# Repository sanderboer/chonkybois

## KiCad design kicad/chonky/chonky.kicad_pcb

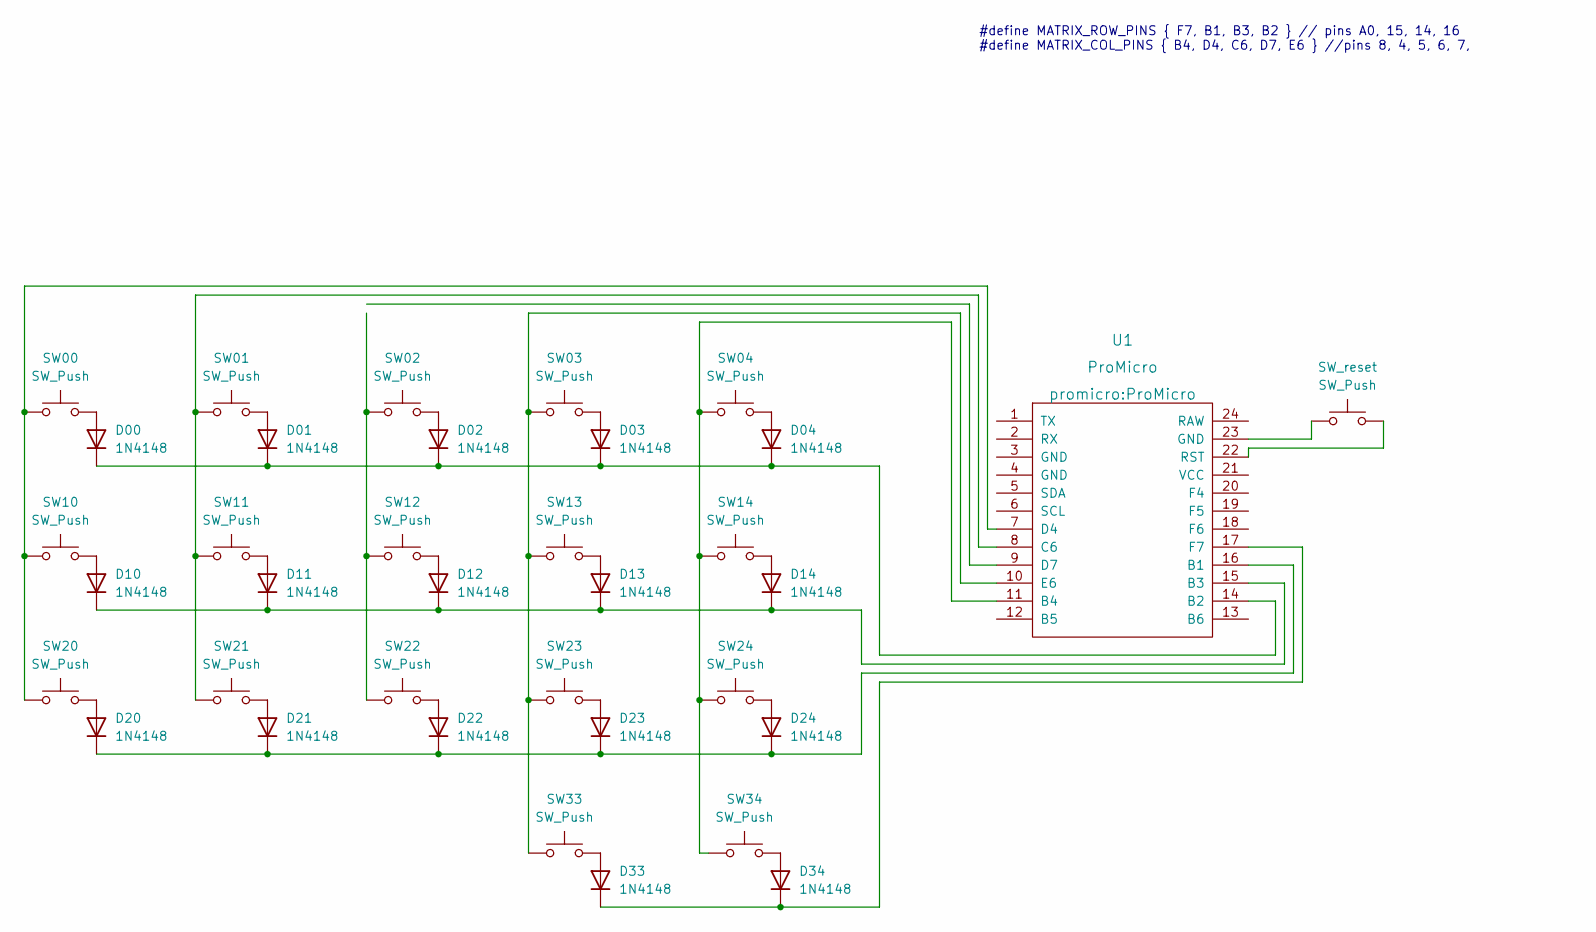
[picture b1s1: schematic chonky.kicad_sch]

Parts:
D00, D01, D02, D03, D04, D10, D11, D12, D13, D14, D20, D21, D22, D23, D24, D33, D34: 1N4148; D_DO-35_SOD27_P7.62mm_Horizontal
SW00, SW01, SW02, SW03, SW04, SW10, SW11, SW12, SW13, SW14, SW20, SW21, SW22, SW23, SW24, SW33, SW34: SW_Push; Kailh_socket_MX
SW_reset: SW_Push; Kailh_socket_MX
U1: ProMicro

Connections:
unnamed: D00.1 (K), D01.1 (K), D02.1 (K), D03.1 (K), D04.1 (K), U1.14 (B2)
unnamed: D00.2 (A), SW00.2
unnamed: D01.2 (A), SW01.2
unnamed: D02.2 (A), SW02.2
unnamed: D03.2 (A), SW03.2
unnamed: D04.2 (A), SW04.2
unnamed: D10.2 (A), SW10.2
unnamed: D11.2 (A), SW11.2
unnamed: D12.2 (A), SW12.2
unnamed: D10.1 (K), D11.1 (K), D12.1 (K), D13.1 (K), D14.1 (K), U1.15 (B3)
unnamed: D13.2 (A), SW13.2
unnamed: D14.2 (A), SW14.2
unnamed: D20.2 (A), SW20.2
unnamed: D21.2 (A), SW21.2
unnamed: D22.2 (A), SW22.2
unnamed: D20.1 (K), D21.1 (K), D22.1 (K), D23.1 (K), D24.1 (K), U1.16 (B1)
unnamed: D23.2 (A), SW23.2
unnamed: D24.2 (A), SW24.2
unnamed: D33.1 (K), D34.1 (K), U1.17 (F7)
unnamed: D33.2 (A), SW33.2
unnamed: D34.2 (A), SW34.2
unnamed: SW00.1, SW10.1, SW20.1, U1.7 (D4)
unnamed: SW01.1, SW11.1, SW21.1, U1.8 (C6)
unnamed: SW02.1, SW12.1, SW22.1
unnamed: SW03.1, SW13.1, SW23.1, SW33.1, U1.10 (E6)
unnamed: SW04.1, SW14.1, SW24.1, SW34.1, U1.11 (B4)
unnamed: SW_reset.1, U1.23 (GND)
unnamed: SW_reset.2, U1.22 (RST)

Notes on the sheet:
#define MATRIX_ROW_PINS { F7, B1, B3, B2 } // pins A0, 15, 14, 16 #define MATRIX_COL_PINS { B4, D4, C6, D7, E6 } //pins 8, 4, 5, 6, 7,

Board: 2 copper layers, 35 parts (0 on the bottom side), 26 nets, no tracks yet.

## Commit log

2021-03-03 the bois are here
2021-03-03 Too lazy to comment
2021-03-09 Create LICENSE
2021-03-12 added more botplate holes for 2.5 mm threaded inserts
2021-03-13 fattened mountplate to 4 mm, more even with ring/pinky rows to help w printing. Mid ring finger tended to jump off print bed bc of lacking adhesion with abs.
2021-07-24 some rethinking going on in generator.
2021-07-25 generator work under progress
2021-08-17 new test of a 4x6
2021-08-28 working on a low-profile one without curvature
2021-08-28 Update generator_3x6_kurtis-flat.blend
    - Fixed bottom pinky screwhole placement
    - Fixed inheritance issues between "case.001", "case-left.001", "case-right.001", and "case-right-bot.001"
    - Fixed mountplate and thumbplate bridge
2021-08-29 Add corne-style STLs
2021-08-29 lowprofile ready for testing
2021-09-10 added an extra curvy variation
2021-09-10 fixed lowprofile some
2021-09-10 lowprofile over
2021-09-11 curvy fixes
2021-09-11 added tenting block in curvy and tried my hand at a really tall tented version
2021-09-14 curvyboi taking shape
2021-11-18 fidget tester stl repaired
2022-06-13 Add lil chonky classic
